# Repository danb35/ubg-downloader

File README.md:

# ubg-downloader
Device to download data from EI UBG-16/MUX-8A

# Introduction
This device developed out of a desire to download data from the [Electronics International](https://www.iflyei.com/) [UBG-16](https://www.iflyei.com/product/ubg-16-ultimate-bar-graph/) in my Mooney aircraft.  EI provide (at an extra cost) a serial cable and software you can install on your laptop, but I didn't want to need to drag a laptop out to the plane to download data; I wanted a small, battery-operated device that would download the data onto an SD card.  This device will do that.

# Status
This project is *archived.*  I no longer have the airplane or any of the EI hardware to test with.  The software and hardware documentation are provided here for anyone to use, and to build on if desired, but I won't be able to provide much in the way of support.  Primary development took place in 2012, so my memory may not be too clear about the details.

But with that said, it worked.  Once the clock was set (I never did get around to developing a UI to do that through the device's software itself), it was just a matter of inserting a couple of AA batteries, plugging it into the plane with a 1/8" stereo audio cable, and downloading.  If you can source the parts and assemble the PCB, it should work for you as well.

# Further information

* [Hardware](hardware.md)
* [Software](software.md)
* [Data Format](data-format.md)

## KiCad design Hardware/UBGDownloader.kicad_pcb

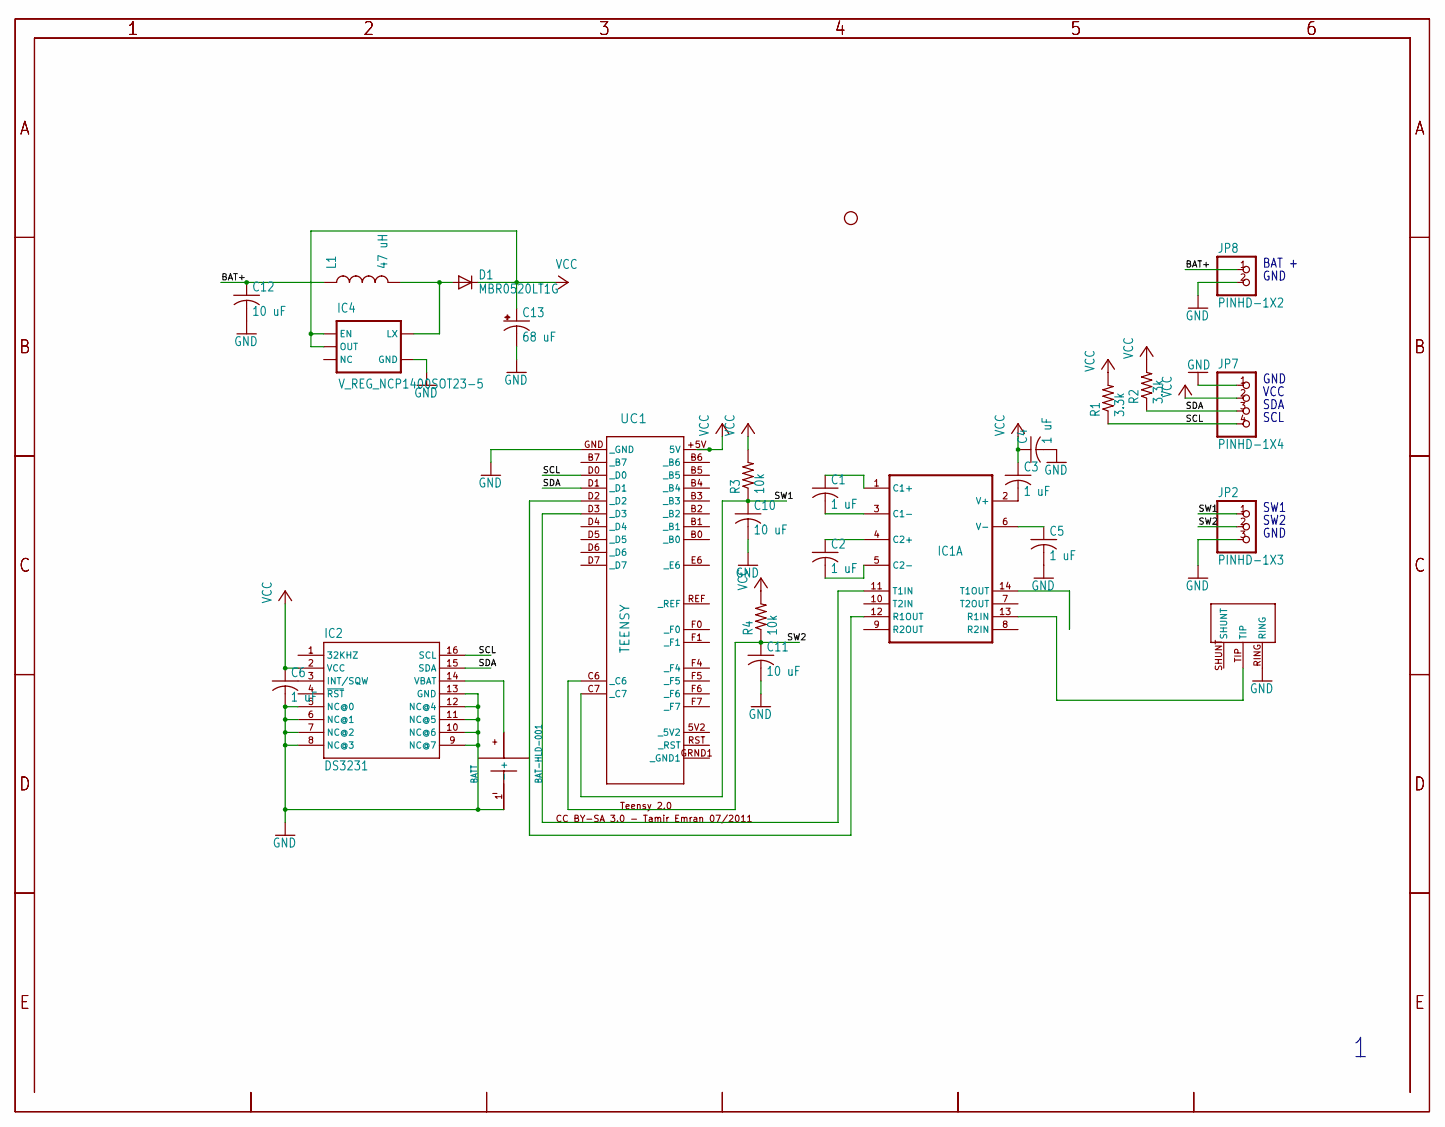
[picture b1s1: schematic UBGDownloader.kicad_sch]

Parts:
BATT: BAT-HLD-001
C1, C2, C3, C4, C5, C6: 1 uF; C0805K
C10, C11, C12: 10 uF; C0805K
C13: 68 uF; B_3528-21R
D1: MBR0520LT1G; SOD-123_MINI-SMA
IC1: MAX3232SE; SO16
IC2: DS3231; SO-16
IC4: V_REG_NCP1400SOT23-5; SOT23-5
JP2: PINHD-1X3; 1X03
JP5: STAND-OFF
JP7: PINHD-1X4; 1X04
JP8: PINHD-1X2; 1X02
L1: 47 uH; CDRH5D28R
R1, R2: 3.3k; R0805
R3, R4: 10k; R0805
U$3: 35RAPC2AVDEFAULT; 35RAPC2AV
UC1: TEENSY

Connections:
BAT+: C12.1, JP8.1, L1.P$1 (1)
GND: BATT.1 (-), C4.2, C5.2, C6.2, C10.2, C11.2, C12.2, C13.-, IC1.15 (GND), IC2.5 (NC@0), IC2.6 (NC@1), IC2.7 (NC@2), IC2.8 (NC@3), IC2.9 (NC@7), IC2.10 (NC@6), IC2.11 (NC@5), IC2.12 (NC@4), IC2.13 (GND), IC4.4 (GND), JP2.3, JP7.1, JP8.2, U$3.RING, UC1.GND (_GND)
unnamed: BATT.2 (+), BATT.3 (+), IC2.14 (VBAT)
unnamed: C1.2, IC1.3 (C1-)
unnamed: C1.1, IC1.1 (C1+)
unnamed: C2.1, IC1.4 (C2+)
unnamed: C2.2, IC1.5 (C2-)
unnamed: C3.2, IC1.2 (V+)
unnamed: C5.1, IC1.6 (V-)
unnamed: IC1.13 (R1IN), U$3.TIP
unnamed: IC1.11 (T1IN), UC1.D3 (_D3)
unnamed: IC1.12 (R1OUT), UC1.D2 (_D2)
unnamed: D1.A, IC4.5 (LX), L1.P$2 (2)
SCL: IC2.16 (SCL), JP7.4, R1.1, UC1.D0 (_D0)
SDA: IC2.15 (SDA), JP7.3, R2.1, UC1.D1 (_D1)
SW1: C10.1, JP2.1, R3.1, UC1.C7 (_C7)
SW2: C11.1, JP2.2, R4.1, UC1.C6 (_C6)
VCC: C3.1, C4.1, C6.1, C13.+, D1.C, IC1.16 (VCC), IC2.2 (VCC), IC4.1 (EN), IC4.2 (OUT), JP7.2, R1.2, R2.2, R3.2, R4.2, UC1.+5V (5V)

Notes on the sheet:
SW2
GND
SDA
VCC
SCL
BAT +
SW1

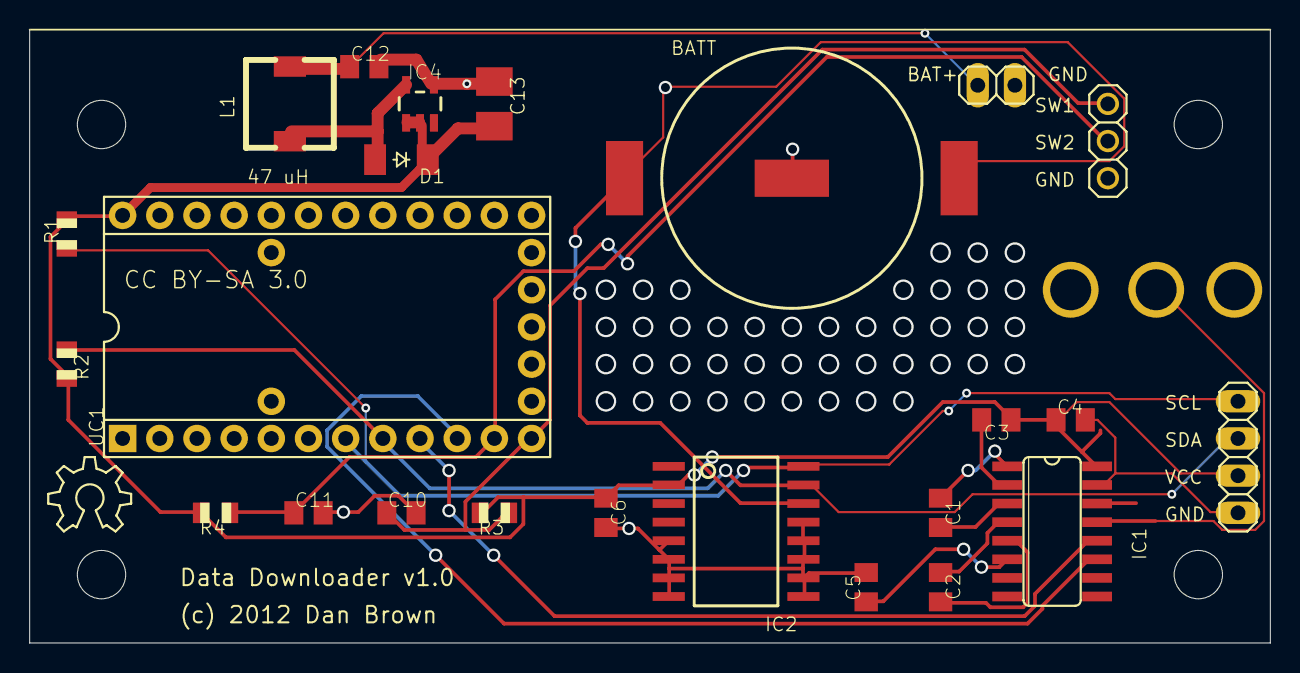
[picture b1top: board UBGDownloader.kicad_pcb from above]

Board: 2 copper layers, 84.8 x 41.9 mm, 30 parts (1 on the bottom side), 18 nets.

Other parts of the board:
JP3, JP4, JP6: STAND-OFF
U$2: OSHW_6X200_NOTEXT

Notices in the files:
Hardware/UBGDownloader.kicad_pcb:
(c) 2012 Dan Brown
Hardware/UBGDownloader.kicad_sch:
CC BY-SA 3.0 - Tamir Emran 07/2011
parts and their libraries:
CC BY-SA 3.0
